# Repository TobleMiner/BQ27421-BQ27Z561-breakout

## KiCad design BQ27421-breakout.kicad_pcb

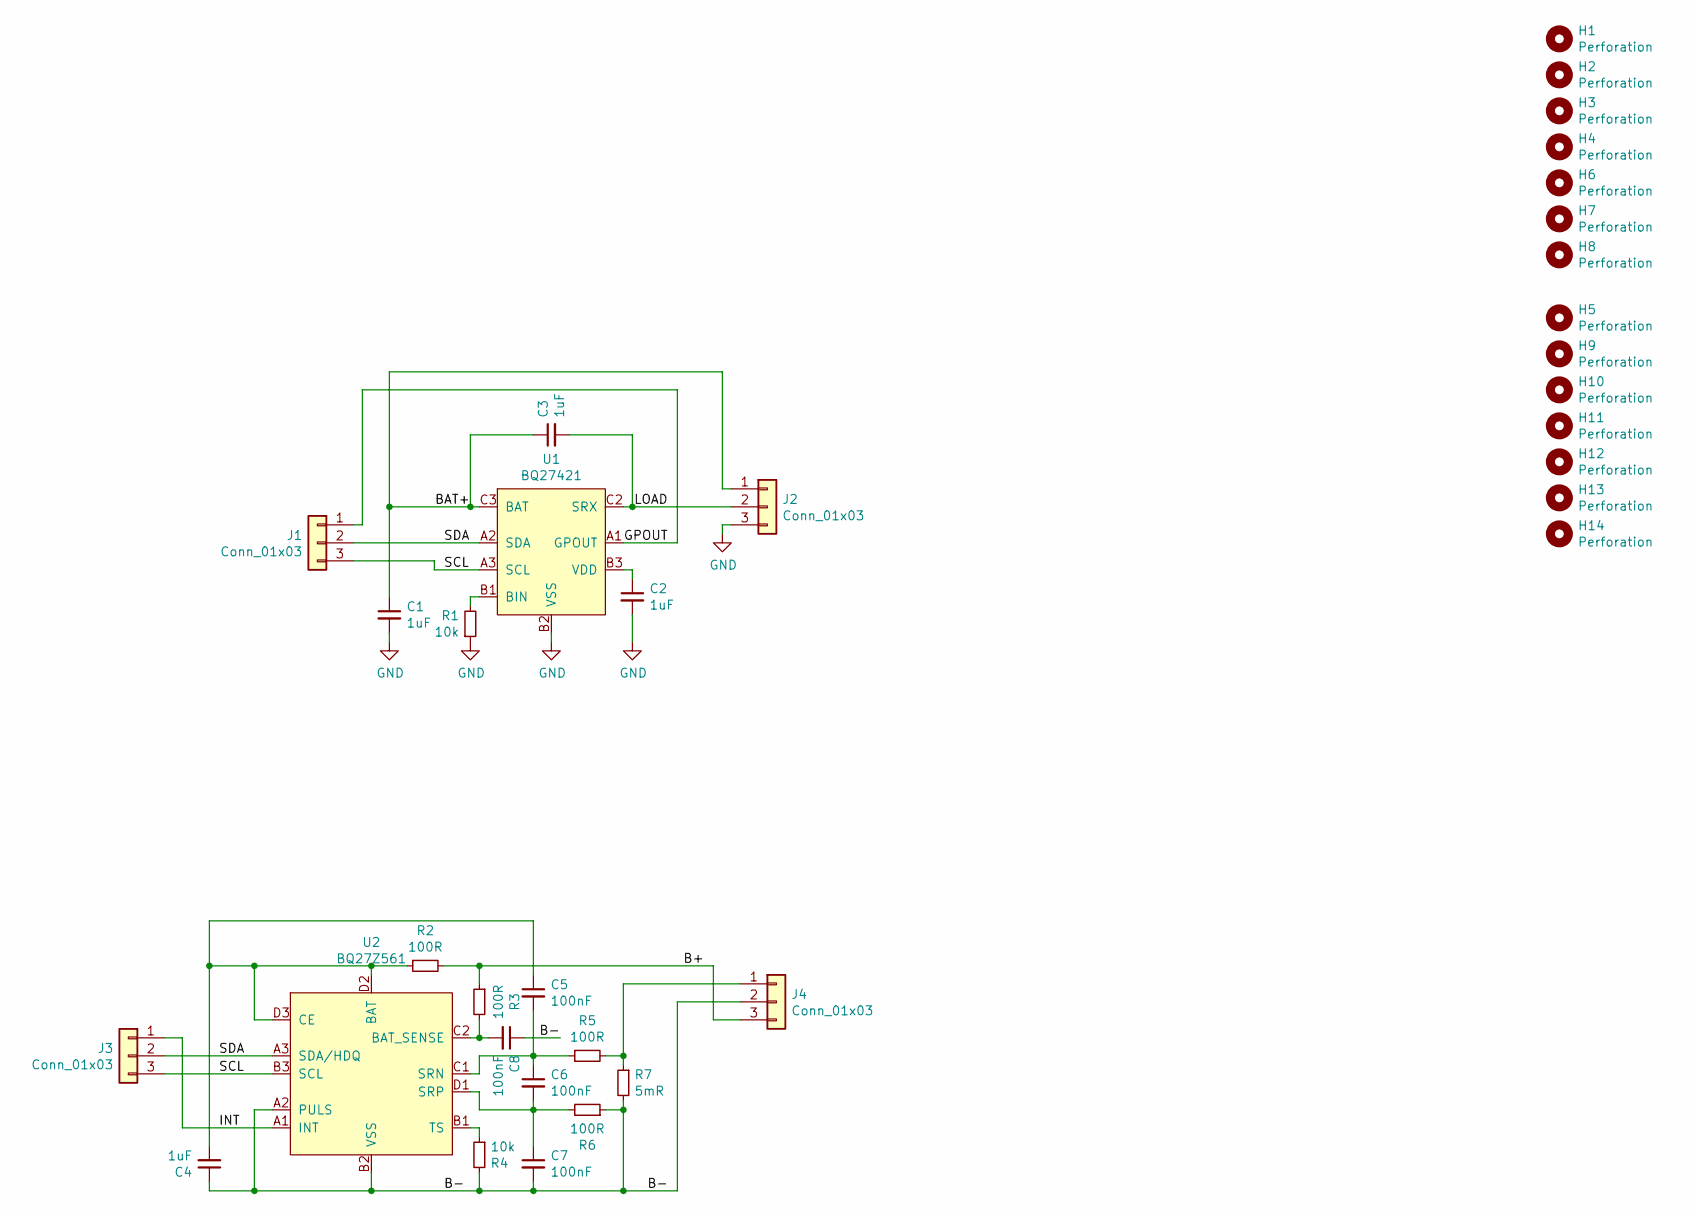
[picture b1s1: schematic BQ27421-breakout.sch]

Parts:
C1, C2, C3, C4: 1uF; C_0402_1005Metric
C5, C6, C7, C8: 100nF; C_0402_1005Metric
H1, H2, H3, H4, H5, H6, H7, H8, H9, H10, H11, H12, H13, H14: Perforation; Perforation_0.4mm
J1, J2, J3, J4: Conn_01x03; PinHeader_1x03_P2.54mm_Vertical
R1, R4: 10k; R_0402_1005Metric
R2, R3, R5, R6: 100R; R_0402_1005Metric
R7: 5mR; R_1206_3216Metric
U1: BQ27421; DSBGA-9_1.6x1.6_P0.5mm
U2: BQ27Z561; DSBGA-12_BQ27Z561_1.7x2.05mm_P0.5mm

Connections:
/B+: J4.3, R2.2, R3.1
/B-: C4.1, C7.2, C8.1, J4.2, R4.2, R6.1, R7.2, U2.A2 (PULS), U2.B2 (VSS)
/BAT+: C1.1, C3.1, J2.1, U1.C3 (BAT)
/GPOUT: J1.1, U1.A1 (GPOUT)
/INT: J3.1, U2.A1 (INT)
/LOAD: C3.2, J2.2, U1.C2 (SRX)
/SCL: J1.3, J3.3, U1.A3 (SCL), U2.B3 (SCL)
/SDA: J1.2, J3.2, U1.A2 (SDA), U2.A3 (SDA/HDQ)
GND: C1.2, C2.2, J2.3, R1.1, U1.B2 (VSS), U1.C1 (VSS)
unnamed: C2.1, U1.B3 (VDD)
unnamed: C4.2, C5.1, R2.1, U2.D2 (BAT), U2.D3 (CE)
unnamed: C5.2, C6.1, R5.1, U2.C1 (SRN)
unnamed: C6.2, C7.1, R6.2, U2.D1 (SRP)
unnamed: C8.2, R3.2, U2.C2 (BAT_SENSE)
unnamed: J4.1, R5.2, R7.1
unnamed: R1.2, U1.B1 (BIN)
unnamed: R4.1, U2.B1 (TS)

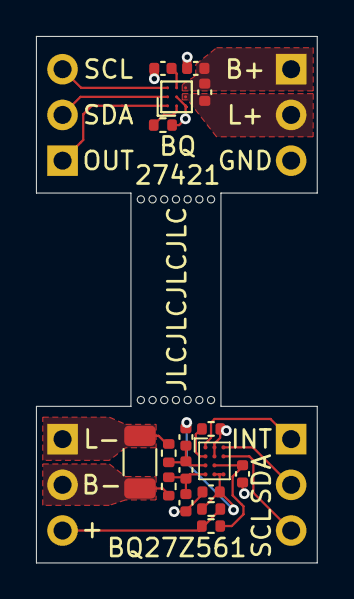
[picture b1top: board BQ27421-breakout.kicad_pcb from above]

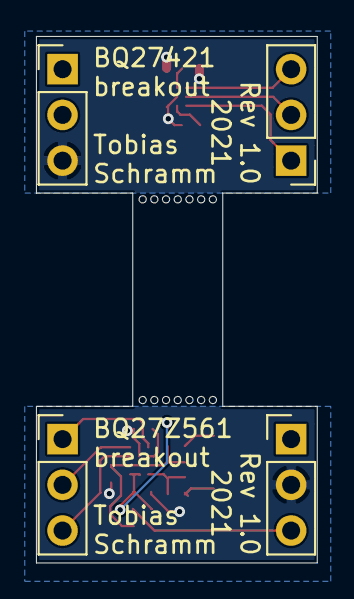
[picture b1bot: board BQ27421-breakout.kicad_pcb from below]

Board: 2 copper layers, 15.6 x 29.2 mm, 35 parts (4 on the bottom side), 17 nets.
